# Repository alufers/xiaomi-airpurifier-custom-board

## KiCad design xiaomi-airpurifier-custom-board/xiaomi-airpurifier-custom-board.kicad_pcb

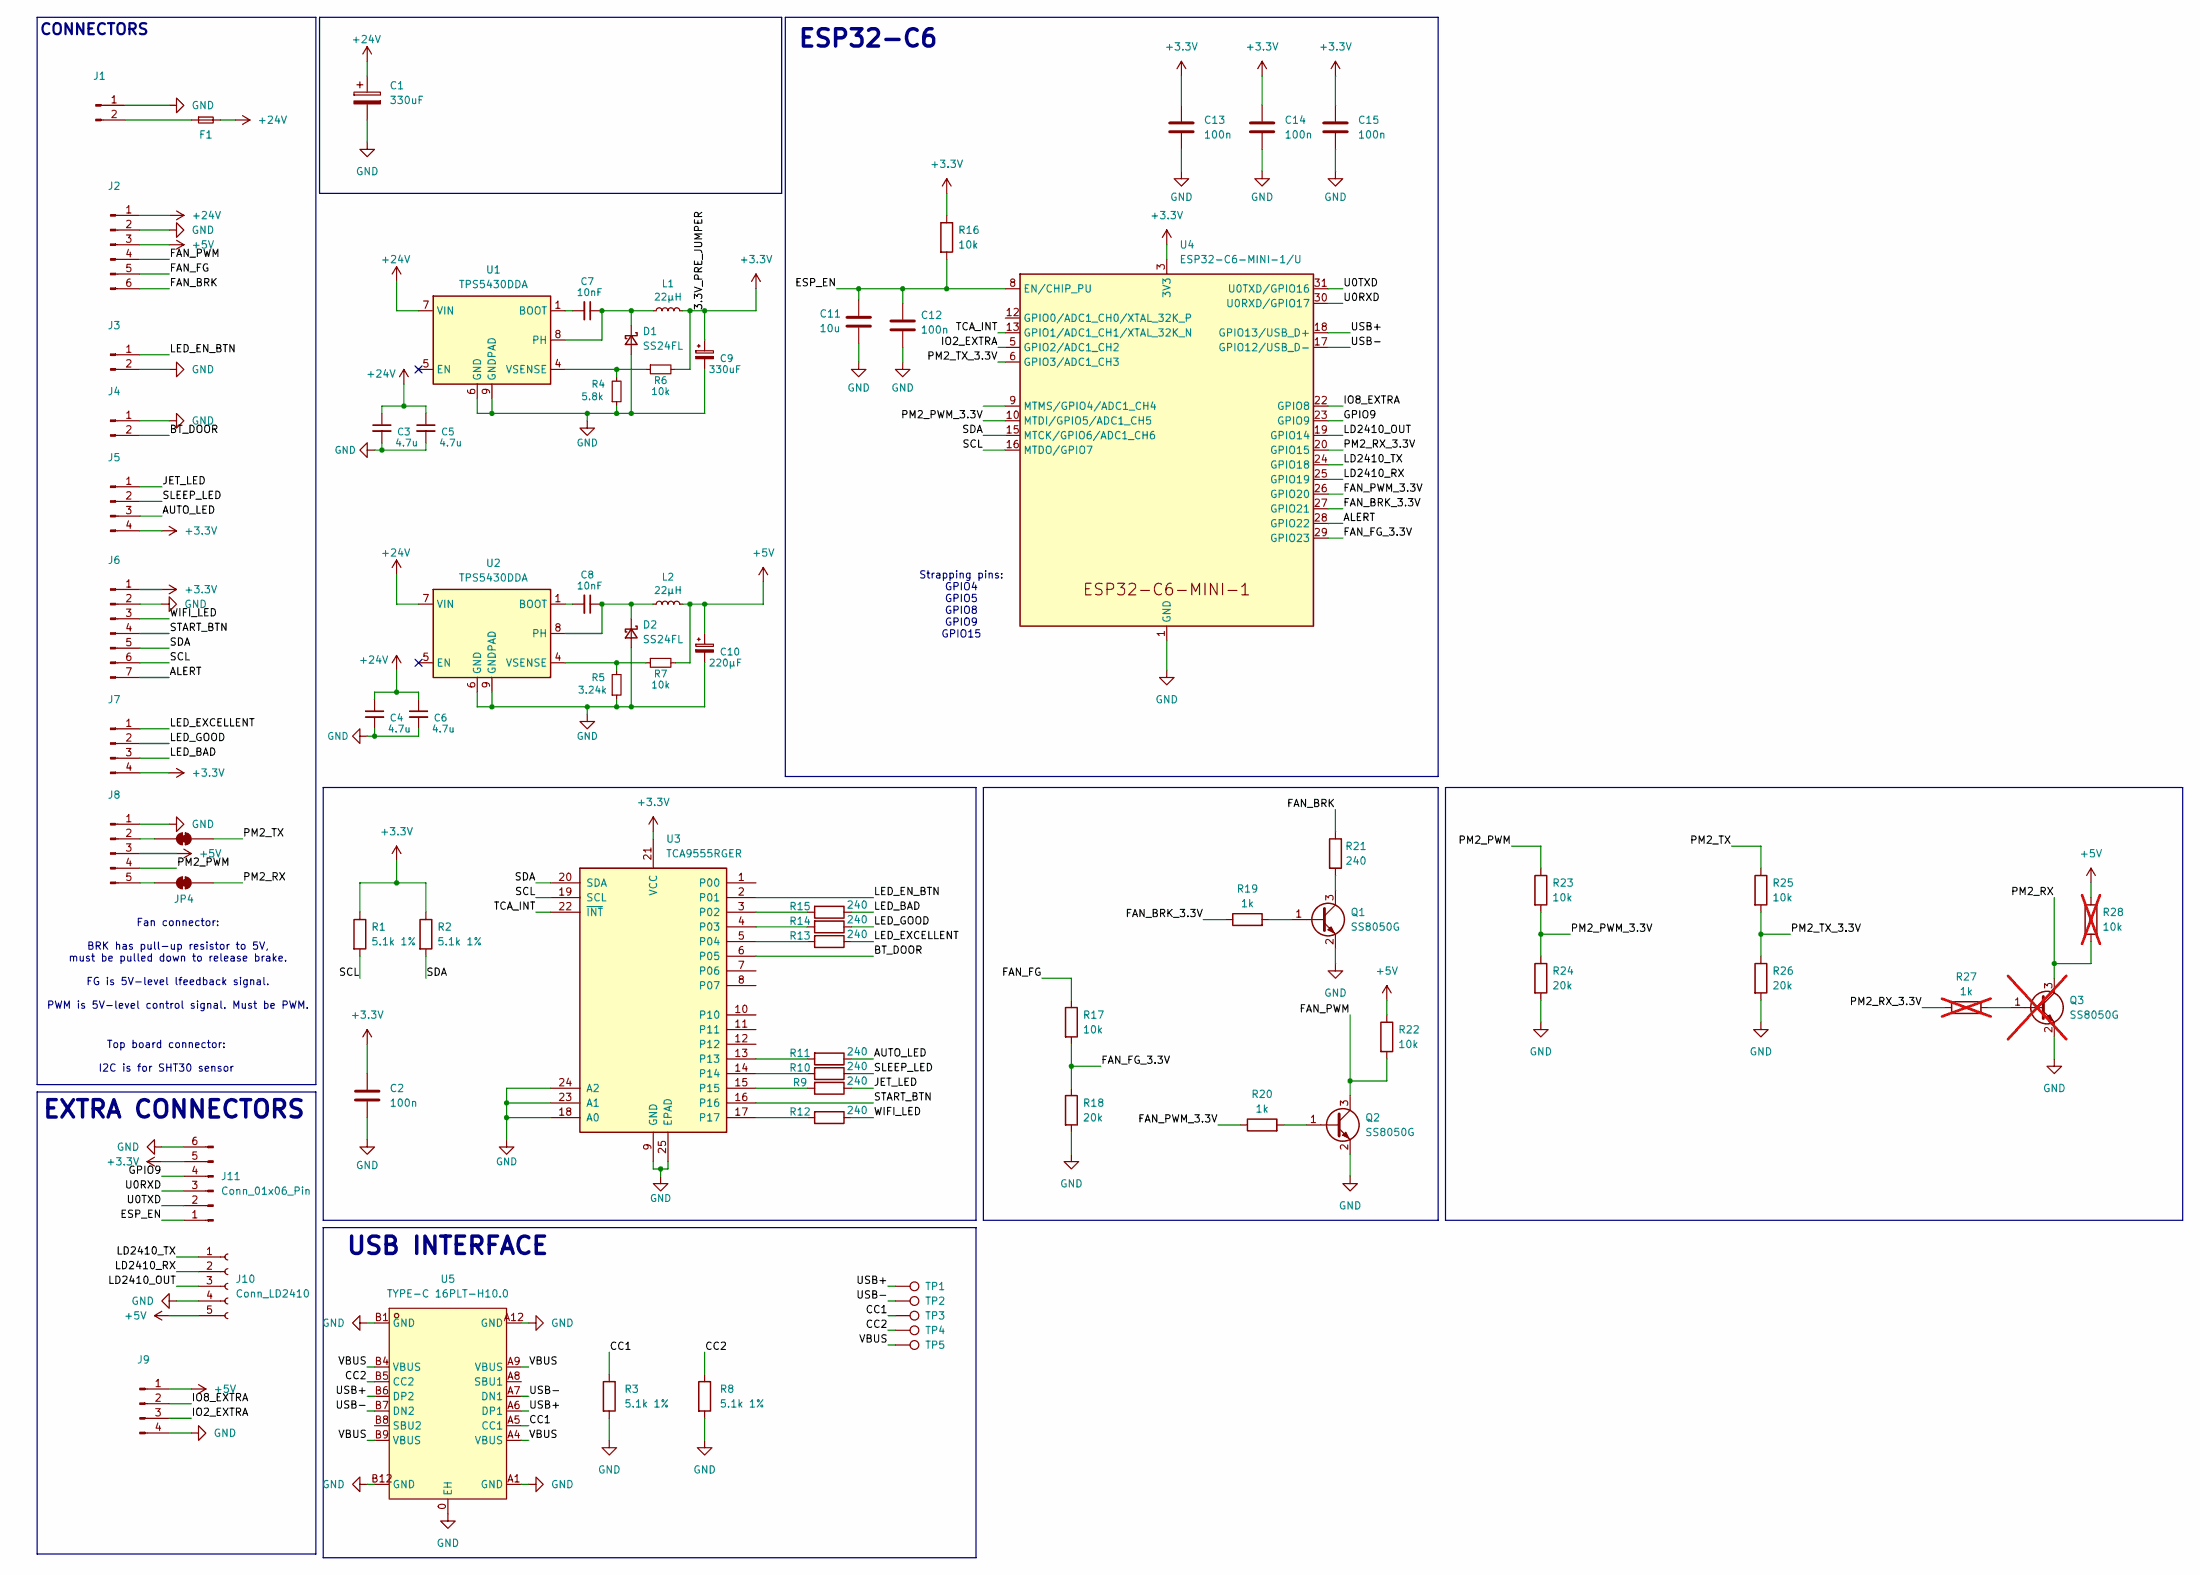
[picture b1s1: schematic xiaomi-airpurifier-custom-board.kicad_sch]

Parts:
C1: 330uF; CP_Elec_10x10.5; LCSC C88796
C2, C12, C13, C14, C15: 100n; C_0603_1608Metric; LCSC C14663
C3, C4, C5, C6: 4.7u; C_0805_2012Metric; LCSC C1779
C7, C8: 10nF; C_0805_2012Metric; LCSC C83170
C9: 330uF; CP_Elec_6.3x7.7; LCSC C47023104
C10: 220µF; CP_Elec_6.3x7.7; LCSC C72496
C11: 10u; C_0603_1608Metric; LCSC C96446
D1, D2: SS24FL; D_SOD-123F; LCSC C489144
F1: BSMD1812-300-24V; Fuse_1812_4532Metric_Pad1.30x3.40mm_HandSolder; LCSC C7500481
J1: XY-VH3.96-2A21; JST_VH_B2PS-VH_1x02_P3.96mm_Horizontal; LCSC C19271421
J2: JST S06B-PASK-2(LF)(SN); JST_PH_S6B-PH-K_1x06_P2.00mm_Horizontal; LCSC C495643
J3: B02B-PASK-1(LF)(SN); JST_PH_B2B-PH-K_1x02_P2.00mm_Vertical; LCSC C398555
J4: BX-PH2.0-2PZZ; JST_PH_B2B-PH-K_1x02_P2.00mm_Vertical; LCSC C18077744
J5: HDGC2001WV-4P; JST_PH_B4B-PH-K_1x04_P2.00mm_Vertical; LCSC C5175232
J6: B07B-PASK(LF)(SN); JST_PH_B7B-PH-K_1x07_P2.00mm_Vertical; LCSC C158042
J7: B04B-PASK-1(LF)(SN); JST_PH_B4B-PH-K_1x04_P2.00mm_Vertical; LCSC C160284
J8: B05B-PASK-1(LF)(SN); JST_PH_B5B-PH-K_1x05_P2.00mm_Vertical; LCSC C160282
J9: JST_PH_B4B-PH-K_1x04_P2.00mm_Vertical
J10: Conn_LD2410; PinSocket_1x05_P2.54mm_Vertical; LCSC C50950
J11: Conn_01x06_Pin; PinHeader_1x06_P2.54mm_Vertical; LCSC C37208
JP4, JP5: SolderJumper_2_Bridged; SolderJumper-2_P1.3mm_Bridged_RoundedPad1.0x1.5mm
L1, L2: 22µH; L_Sunlord_MWSA1003S; LCSC C475917
Q1, Q2: SS8050G; SOT-23; LCSC C164886
Q3: SS8050G; SOT-23; LCSC C164886; not fitted
R1, R2, R3, R8: 5.1k 1%; R_0603_1608Metric; LCSC C23186
R4: 5.8k; R_0603_1608Metric; LCSC C862231
R5: 3.24k; R_0603_1608Metric; LCSC C2933197
R6, R7, R16, R17, R22, R23, R25: 10k; R_0603_1608Metric; LCSC C25804
R9, R10, R11, R12, R13, R14, R15, R21: 240; R_0603_1608Metric_Pad0.98x0.95mm_HandSolder; LCSC C2907130
R18, R24, R26: 20k; R_0603_1608Metric; LCSC C105575
R19, R20: 1k; R_0603_1608Metric; LCSC C22548
R27: 1k; R_0603_1608Metric; LCSC C22548; not fitted
R28: 10k; R_0603_1608Metric; LCSC C25804; not fitted
TP1, TP2, TP3, TP4, TP5: TestPoint; TestPoint_Pad_D1.0mm
U1, U2: TPS5430DDA; TI_SO-PowerPAD-8_ThermalVias; LCSC C9864
U3: TCA9555RGER; VQFN-24-1EP_4x4mm_P0.5mm_EP2.45x2.45mm; LCSC C42420609
U4: ESP32-C6-MINI-1/U; ESP32-C6-MINI-1; LCSC C5736265
U5: TYPE-C 16PLT-H10.0; TYPE-C-SMD_USB4120-03-C; LCSC C3151749

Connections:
+3.3V: C2.1, C9.1, C13.1, C14.1, C15.1, J5.4, J6.1, J7.4, J11.5, L1.2, R1.1, R2.1, R6.2, R16.1, U3.21 (VCC), U4.3 (3V3)
+5V: C10.1, J2.3, J8.3, J9.1, J10.5, L2.2, R7.2, R22.1, R28.1
+24V: C1.1, C3.1, C4.1, C5.1, C6.1, F1.2, J2.1, U1.7 (VIN), U2.7 (VIN)
/ALERT: J6.7, U4.28 (GPIO22)
/AUTO_LED: J5.3, R11.1
/BT_DOOR: J4.2, U3.6 (P05)
/CC1: R3.1, TP3.1 (1_1), U5.A5 (CC1)
/CC2: R8.1, TP4.1 (1_1), U5.B5 (CC2)
/ESP_EN: C11.1, C12.1, J11.1, R16.2, U4.8 (EN/CHIP_PU)
/FAN_BRK: J2.6, R21.1
/FAN_BRK_3.3V: R19.1, U4.27 (GPIO21)
/FAN_FG: J2.5, R17.1
/FAN_FG_3.3V: R17.2, R18.1, U4.29 (GPIO23)
/FAN_PWM: J2.4, Q2.3 (C), R22.2
/FAN_PWM_3.3V: R20.1, U4.26 (GPIO20)
/GPIO9: J11.4, U4.23 (GPIO9)
/IO2_EXTRA: J9.3, U4.5 (GPIO2/ADC1_CH2)
/IO8_EXTRA: J9.2, U4.22 (GPIO8)
/JET_LED: J5.1, R9.1
/LD2410_OUT: J10.3, U4.19 (GPIO14)
/LD2410_RX: J10.2, U4.25 (GPIO19)
/LD2410_TX: J10.1, U4.24 (GPIO18)
/LED_BAD: J7.3, R15.1
/LED_EN_BTN: J3.1, U3.2 (P01)
/LED_EXCELLENT: J7.1, R13.1
/LED_GOOD: J7.2, R14.1
/PM2_PWM: J8.4, R23.1
/PM2_PWM_3.3V: R23.2, R24.1, U4.10 (MTDI/GPIO5/ADC1_CH5)
/PM2_RX: JP4.2 (B), Q3.3 (C), R28.2
/PM2_RX_3.3V: R27.1, U4.20 (GPIO15)
/PM2_TX: JP5.2 (B), R25.1
/PM2_TX_3.3V: R25.2, R26.1, U4.6 (GPIO3/ADC1_CH3)
/SCL: J6.6, R1.2, U3.19 (SCL), U4.16 (MTDO/GPIO7)
/SDA: J6.5, R2.2, U3.20 (SDA), U4.15 (MTCK/GPIO6/ADC1_CH6)
/SLEEP_LED: J5.2, R10.1
/START_BTN: J6.4, U3.16
/TCA_INT: U3.22 (~INT), U4.13 (GPIO1/ADC1_CH1/XTAL_32K_N)
/U0RXD: J11.3, U4.30 (U0RXD/GPIO17)
/U0TXD: J11.2, U4.31 (U0TXD/GPIO16)
/USB+: TP1.1 (1_1), U4.18 (GPIO13/USB_D+), U5.A6 (DP1), U5.B6 (DP2)
/USB-: TP2.1 (1_1), U4.17 (GPIO12/USB_D-), U5.A7 (DN1), U5.B7 (DN2)
/VBUS: TP5.1 (1_1), U5.A4 (VBUS), U5.A9 (VBUS), U5.B4 (VBUS), U5.B9 (VBUS)
/WIFI_LED: J6.3, R12.1
GND: C1.2, C2.2, C3.2, C4.2, C5.2, C6.2, C9.2, C10.2, C11.2, C12.2, C13.2, C14.2, C15.2, D1.2 (A), D2.2 (A), J1.1, J2.2, J3.2, J4.1, J6.2, J8.1, J9.4, J10.4, J11.6, Q1.2 (E), Q2.2 (E), Q3.2 (E), R3.2, R4.1, R5.1, R8.2, R18.2, R24.2, R26.2, U1.6 (GND), U1.9 (GNDPAD), U2.6 (GND), U2.9 (GNDPAD), U3.9 (GND), U3.18 (A0), U3.23 (A1), U3.24 (A2), U3.25 (EPAD), U4.1 (GND), U4.2 (GND), U4.11 (GND), U4.14 (GND), U4.36 (GND), U4.37 (GND), U4.38 (GND), U4.39 (GND), U4.40 (GND), U4.41 (GND), U4.42 (GND), U4.43 (GND), U4.44 (GND), U4.45 (GND), U4.46 (GND), U4.47 (GND), U4.48 (GND), U4.49 (GND), U4.50 (GND), U4.51 (GND), U4.52 (GND), U4.53 (GND), U5.0 (EH), U5.A1 (GND), U5.A12 (GND), U5.B1 (GND), U5.B12 (GND)
unnamed: C7.1, D1.1 (K), L1.1, U1.8 (PH)
unnamed: C8.1, D2.1 (K), L2.1, U2.8 (PH)
unnamed: F1.1, J1.2
unnamed: J8.2, JP5.1 (A)
unnamed: J8.5, JP4.1 (A)
unnamed: Q1.1 (B), R19.2
unnamed: Q1.3 (C), R21.2
unnamed: Q2.1 (B), R20.2
unnamed: Q3.1 (B), R27.2
unnamed: C7.2, U1.1 (BOOT)
unnamed: R4.2, R6.1, U1.4 (VSENSE)
unnamed: C8.2, U2.1 (BOOT)
unnamed: R5.2, R7.1, U2.4 (VSENSE)
unnamed: R15.2, U3.3 (P02)
unnamed: R14.2, U3.4 (P03)
unnamed: R13.2, U3.5 (P04)
unnamed: R11.2, U3.13
unnamed: R10.2, U3.14
unnamed: R9.2, U3.15
unnamed: R12.2, U3.17

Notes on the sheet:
EXTRA CONNECTORS
CONNECTORS
Strapping pins: GPIO4 GPIO5 GPIO8 GPIO9 GPIO15
Top board connector: I2C is for SHT30 sensor
ESP32-C6
USB INTERFACE
Fan connector: BRK has pull-up resistor to 5V, must be pulled down to release brake. FG is 5V-level lfeedback signal. PWM is 5V-level control signal. Must be PWM.

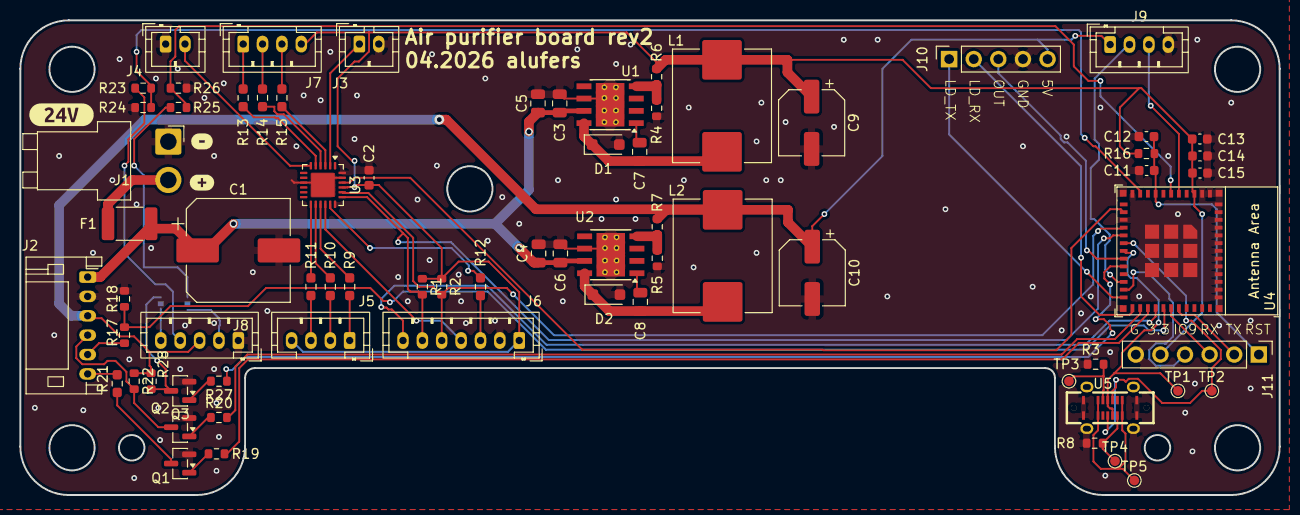
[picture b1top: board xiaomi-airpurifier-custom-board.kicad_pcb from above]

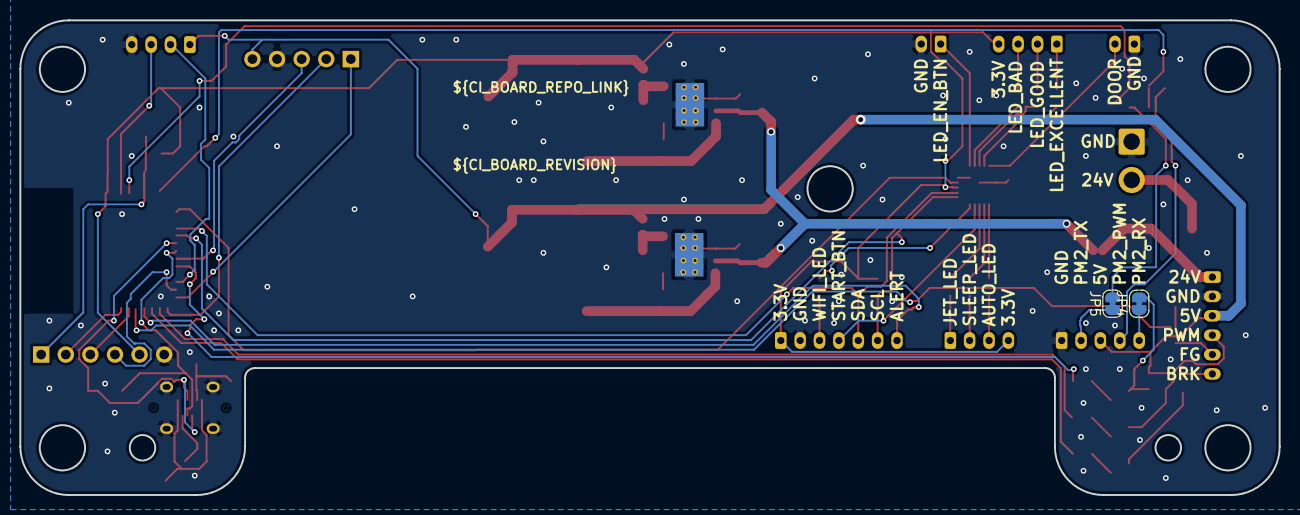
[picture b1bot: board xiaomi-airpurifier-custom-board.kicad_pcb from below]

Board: 2 copper layers, 130.0 x 49.0 mm, 77 parts (2 on the bottom side), 64 nets.

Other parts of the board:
kibuzzard-69EA0A86: G***; kibuzzard-69EA0A86
kibuzzard-69EA0AD8: G***; kibuzzard-69EA0AD8
kibuzzard-69EA09FB: G***; kibuzzard-69EA09FB

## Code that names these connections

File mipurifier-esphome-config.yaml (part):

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      sorting_weight: 40

i2c:
  sda: GPIO6
  scl: GPIO7
  scan: true

uart:
  - id: uart_ld2410
    tx_pin: GPIO18
    rx_pin: GPIO19
    baud_rate: 256000
    parity: NONE
    stop_bits: 1
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    update_interval: 30s

  - platform: pulse_counter
    pin: GPIO23
    id: fan_rpm
    name: "Fan RPM"
    unit_of_measurement: "RPM"
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  - platform: gpio
    name: "Radar Presence"
    pin:
      number: GPIO14
      mode: INPUT
    web_server:
      sorting_group_id: sorting_group_radar
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        sorting_group_id: sorting_group_radar

  - platform: gpio
    pin: GPIO5
    id: pm1003ph_pwm_signal
    internal: true

output:
  - platform: ledc
    id: out_fan
    pin: GPIO20
    frequency: 40Hz

  - platform: template
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  - platform: gpio
    name: "Unbrake"
    id: unbrake
    pin: GPIO21
    internal: true

  - platform: ld2410
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
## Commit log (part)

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2026-04-23 Add CI
2026-04-23 Show DRC errors in github actions log
2026-04-23 change clearance violation to warning
2026-04-23 fix CI shit, generate ibom
2026-04-24 Add variable definition for QR code to see what happens
